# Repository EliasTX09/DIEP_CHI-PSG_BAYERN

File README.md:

# ⛳ Golf Battle 3D – Arcade-Multiplayer-Minigolf für Android (Godot 4)

Echtes 3D-Arcade-Minigolf: 15 Bahnen in 4 Welten, eingebettet in Täler mit Bergen, Klippen, Wäldern und Schluchten,
riskante Abkürzungen, Loopings, Kanonen, Teleporter, Hämmer, Bäche, Lava und Wasser,
bis zu 6 Spieler gleichzeitig, Bots für den Offline-Modus, Schlägertasche mit Upgrades, Truhen, Ligen
und ein täglicher „Golden Shot“. **Alles** – Bahnen, Modelle, Effekte, Shader und Sounds – wird per Code erzeugt.
Es gibt keine `.glb`-, `.fbx`- oder `.wav`-Dateien im Projekt.

> Engine: **Godot 4.5** (GDScript, Mobile-Renderer, Jolt Physics) · Backend: **Supabase** (optional) ·
> Build: **GitHub Actions** → `GolfBattle3D.apk`
> Hochformat (einhändig) · Web-Portal für Accounts in [`webapp/`](webapp) (GitHub Pages)
> Die `index.html` im Repo-Root gehört nicht zum Spiel.

> **Umbau-Stand:** Hochformat-Hauptmenü (Arena-Auswahl mit 3D-Hintergrund, Tab-Leiste Spielen · Tasche · Pass ·
> Freunde · Shop), Hochformat-HUD, kostenloser Battle Pass (28-Tage-Saisons, 30 Stufen), Bahnen in Berg-Tälern
> statt im offenen Wasser, eine riskante Abkürzung pro Bahn, Hindernisse auf der Bahn (Bach, Rough, Baumstämme,
> Felsen) und die neue Ziel-Vorschau (Gummiband + Punkt-Kette) sind fertig.
> Noch offen: Flyover-Vorschau, Trophäen pro Bahn, adaptive Bots, Clans.

---

## Schnellstart in 4 Schritten

### 1. Supabase einrichten (optional – ohne Backend läuft das Spiel offline mit Bots)

1. Auf [supabase.com](https://supabase.com) ein kostenloses Projekt anlegen.
2. **SQL Editor → New query**: den kompletten Inhalt von [`supabase_schema.sql`](supabase_schema.sql) einfügen
   und **Run** drücken. Das Skript ist wiederholbar (zweimal ausführen schadet nicht) und legt an:
   `profiles`, `clubs`, `inventory`, `friends`, `lobbies`, `lobby_invites`, `match_results`, `game_link_codes`
   inklusive Row-Level-Security, dazu den Storage-Bucket **`avatars`** für Profilbilder (öffentlich lesbar, max. 512 KB).
3. **Authentication → Sign In / Providers**:
   - **„Allow anonymous sign-ins“ einschalten** (für den Sofort-Gast-Login per Geräte-ID).
   - **Email** aktiviert lassen (zum Verknüpfen des Gast-Accounts mit E-Mail + Passwort).
     Für schnelle Tests kannst du „Confirm email“ ausschalten.
4. **Authentication → URL Configuration**: als **Site URL** und unter **Redirect URLs** die Adresse deines
   Web-Portals eintragen (z.B. `https://<dein-name>.github.io/<repo>/`), damit Bestätigungs- und
   Passwort-Mails zurück aufs Portal führen.
5. **Project Settings → API**: die **Project URL** und den **anon public**-Key kopieren.
   ⚠️ **Niemals** den `service_role`-Key verwenden – der gehört nie in eine App.

### 2. Zugangsdaten eintragen – eine der beiden Varianten

**Variante A (empfohlen): GitHub Secrets** – dann stehen die Werte nicht im Repository.
GitHub → dein Repo → **Settings → Secrets and variables → Actions → New repository secret**:

| Name | Wert |
|---|---|
| `SUPABASE_URL` | `https://xxxx.supabase.co` |
| `SUPABASE_ANON_KEY` | dein anon public Key |
| `WEB_PORTAL_URL` (optional) | Adresse des Web-Portals; ohne Angabe: `https://<besitzer>.github.io/<repo>/` |

Der Workflow schreibt sie beim Build in `config/backend.cfg`.

**Variante B:** direkt in [`config/backend.cfg`](config/backend.cfg) eintragen:

```ini
[supabase]
url="https://xxxx.supabase.co"
anon_key="eyJhbGciOi..."
```

Solange dort die Platzhalter stehen, startet das Spiel im **Offline-Modus** (Bots, lokaler Speicherstand).

### 3. Auf GitHub pushen

Der Workflow [`.github/workflows/build_android.yml`](.github/workflows/build_android.yml) läuft bei jedem Push auf
`main` (und auf Entwicklungs-Branches `ccr-*`) sowie manuell über **Actions → Build Android APK → Run workflow**.
Er

1. nutzt Godot 4.5.2 mit Export-Templates, Android-SDK und Java 17 (Docker-Image `barichello/godot-ci:4.5.2`),
2. erzeugt einen Debug-Keystore,
3. importiert das Projekt und bricht bei jedem Skriptfehler ab,
4. beweist, dass wirklich **Jolt Physics** rechnet (Physik-Fingerabdruck),
5. führt einen Headless-Smoke-Test aus (Logik, Physik, alle Bahnen, Bots, komplette Partie, Touch-Gesten, Menü),
6. exportiert **`GolfBattle3D.apk`** und lädt sie als **Artifact** hoch,
7. veröffentlicht sie bei Pushes auf `main` zusätzlich als **GitHub Release** (`build-<Nummer>`).

Parallel laufen ein Shader-Check mit Software-Rendering (inkl. Screenshots) und ein Test des SQL-Schemas
gegen eine echte PostgreSQL-Datenbank.

### 4. APK herunterladen und installieren

1. GitHub → **Actions** → letzter grüner Lauf von „Build Android APK“ → unten bei **Artifacts** auf
   **GolfBattle3D-apk** klicken (ZIP entpacken) – oder bei Builds von `main` unter **Releases** die APK laden.
2. APK aufs Handy kopieren (oder direkt am Handy herunterladen) und antippen.
3. Android fragt nach **„Installation aus unbekannten Quellen“** → für den Browser/Dateimanager erlauben.
4. Installieren, starten – fertig. Das Spiel läuft im Hochformat.

Voraussetzungen am Gerät: Android 7+ mit **arm64** (praktisch alle Geräte seit ca. 2017).
Der Mobile-Renderer nutzt Vulkan; auf Geräten ohne Vulkan wechselt Godot automatisch auf OpenGL.

### 5. Web-Portal veröffentlichen (Account, Profilbild, Freunde)

Das Portal liegt in [`webapp/`](webapp) – reines HTML/CSS/JavaScript ohne externe Bibliotheken.

1. GitHub → **Settings → Pages → Source: „GitHub Actions“** (falls auf GitHub Pages dieses Repositorys schon
   eine andere Seite läuft: Achtung, das Portal ersetzt sie – dann lieber ein eigenes Repository dafür nutzen).
2. Die Secrets `SUPABASE_URL` und `SUPABASE_ANON_KEY` setzen (wie oben).
3. **Actions → „Web-Portal veröffentlichen“ → Run workflow** (läuft bewusst nur manuell und vom Standard-Branch).

**So verbindet man das Spiel mit dem Web-Account:**
1. Im Spiel: **Profil → „Account verknüpfen / Registrieren“** öffnet das Portal im Browser.
2. Dort registrieren bzw. einloggen, Profilbild hochladen, Freunde verwalten.
3. **„Spiel-Code erzeugen“** (Passwort bestätigen) → 8-stelliger Code, 10 Minuten und nur einmal gültig.
4. Code im Spiel unter **Profil → Spiel-Code → Einlösen** eingeben. Das Spiel erhält dabei eine **eigene** Anmeldung
   (die Browser-Sitzung wird nie weitergegeben) und speichert sie verschleiert in `user://auth.json`.
5. Hatte das Spiel schon Fortschritt als Gast und der Web-Account ebenfalls, wird der Stand des Accounts geladen
   und der Gast-Stand als Sicherung (`user://save_backup_*.json`) abgelegt – es geht nichts still verloren.
   Ist der Web-Account neu, übernimmt er den Gast-Fortschritt.

Ein Direkt-Sprung vom Browser zurück ins Spiel (Deep-Link) ist **nicht** eingebaut – dafür bräuchte die APK
einen eigenen Android-Build mit Intent-Filter. Der Code wird deshalb abgetippt.

---

## Steuerung

| Geste | Wirkung |
|---|---|
| Am Ball ziehen und loslassen | Schlag: nach hinten ziehen wie ein Gummiband (das Band spannt sich hinter dem Ball zum Finger), loslassen schießt nach vorn. Vorn zeigt eine Punkt-Kette auf dem Boden, wo der Ball aufkommt, abprallt und ausrollt (echte Simulation). Länge der Kette = Guide-Wert des Schlägers, Größe des Landerings = Accuracy |
| Ein Finger irgendwo sonst | Kamera 360° drehen und neigen |
| Zwei Finger | Pinch-Zoom |
| Auge-Button | Vogelperspektive |
| „ROLLEN / CHIP“ | Putt am Boden oder Chip-Schlag in die Luft |
| Spin-Widget | Topspin, Backspin, Seiten-Effet |
| Smiley-Button | Emotes & Quick-Chat („Nice Shot!“, „Oops!“, 🔥, 😂 …) |
| Android-Zurück | schließt Fenster bzw. fragt vor dem Beenden |

## Inhalte

- **Welten & Bahnen (15 + Daily):** Emerald Valley (5), Volcano Canyon (4), Cyber Neon City (3), Pirate Cove / Sky Ruins (3),
  jede Welt mit eigenem Himmel, Licht, Nebel und Shadern (Wasser, Lava, Neon-Hologramm, Holzplanken, Wasserfall …).
- **Landschaft:** Jede Bahn liegt in einem Tal: Randstreifen, Wiesen-Böschungen, Felsterrassen und Klippen,
  Bergrücken mit Schnee, ein Bergkranz im Nebel, Tannen-/Laub-/Palmenwälder bzw. tote Bäume und Hochhäuser (Neon),
  Wasserfall-Kaskade oder Lavastrom, Piratenbucht mit Meer und Schiff. Unter Sprüngen und Stücken ohne Bande klafft
  eine Schlucht. Wer das Gelände neben der Bahn berührt, ist **aus** (+1 Strafschlag).
- **Abkürzungen:** Auf jeder Bahn außer der geraden Einsteiger-Bahn e1 (und dem Golden Shot) gibt es eine Öffnung in
  der Bande: ein schmaler Steg ohne Banden führt über eine Schlucht durch ein Felsentor zu einem Sprungpad, das den
  Ball mit Schwung aufs Grün (bzw. ein späteres Fairway-Stück) schießt. Vom Steg gerollt = Schlucht = Aus, zu
  langsam = der Ball bleibt auf dem Steg; wer seitlich versetzt oder mit falschem Tempo aufs Pad kommt, landet versetzt.
- **Hindernisse:** Bäche quer über die Bahn mit schmalem Holzsteg, tiefes Rough am Rand, Baumstämme und Felsbrocken,
  Lianen-Bögen, Sandbunker.
- **Bahn-Baukasten:** Rampen, Steilkurven, Spiralen, Loopings, Brücken, Lücken, Boost-Pads, Windzonen, Teleporter,
  Kanonen, Laser-Tore, Sandbunker, Windmühlen, Pendel-Hämmer, Schiebeblöcke, fahrende Plattformen.
- **Multiplayer:** Gast-Login per Geräte-ID, Verknüpfen mit E-Mail/Passwort, Spielername, Avatar-Farbe und -Rahmen,
  bis zu 6 Spieler gleichzeitig (alle schlagen parallel), Live-Rangliste, Emotes, Freunde (Suche per Name oder
  Freundes-Code, Anfragen, Online-Status), private Lobby mit 4-stelligem Raum-Code oder Einladung, Welt und 3/5/9 Runden.
- **Progression:** 16 Schläger (4 Kategorien × 4 Seltenheiten, Werte Power/Accuracy/Spin/Guide, Upgrades mit Coins + Karten),
  6 Bälle mit kleinen Boni, 6 Trails, 5 Loch-Explosionen mit Screen-Shake und Bass, 4 Truhen-Slots mit Timern
  (oder sofort per Gems), Trophäen, 5 Ligen und Trophäen-Pfad.
- **Extras:** Style-Punkte („Air Time!“, „Bank Shot!“, „Close Call!“, Hole-in-One) mit Bonus-Coins,
  Golden Shot (ein Schlag pro Tag, Belohnung nach Abstand zur Fahne), Replay des besten Schlags in Zeitlupe.
- **Sound:** prozeduraler Synthesizer (`AudioStreamGenerator`) – Abschlag je nach Kraft, Abpraller auf Holz/Stein/Metall,
  Wind bei hohen Sprüngen, Wasser-/Lava-Platscher, Loch-Sound + Fanfare, UI-Klicks, Truhen-Jingle.

## Projektstruktur

```
project.godot                     Godot 4.5, Mobile-Renderer, Jolt Physics, Hochformat (720 x 1280), MSAA, Schatten
export_presets.cfg                Android-Export (arm64, INTERNET, ACCESS_NETWORK_STATE, VIBRATE)
supabase_schema.sql               Tabellen, RLS-Policies, Trigger, Spiel-Code-Funktionen, Storage-Bucket "avatars"
config/backend.cfg                Supabase-URL + anon-Key + Web-Portal-Adresse (Platzhalter = Offline-Modus)
.github/workflows/build_android.yml   Tests + APK + Schema-Test + Portal-Browsertest
.github/workflows/pages.yml           Web-Portal auf GitHub Pages veröffentlichen (manuell)
webapp/                           Web-Portal: index.html, app.js, style.css, config.js
scenes/                           MainMenuView.tscn, Game.tscn, GameHUD.tscn
shaders/                          17 eigene Shader (Gelände, Gras/Grün, Sand, Wasser, Lava, Himmel, Neon, Portal, Ball-Skins …)
scripts/autoload/                 GameManager (Speicherstand, Wirtschaft, Truhen, Ligen),
                                  AuthManager (Login, Session, Web-Code), ProfileManager (Profilbild),
                                  NetworkManager (Profil-Sync, Freunde, Lobbys, Realtime), SoundManager (Synthesizer)
scripts/data/Catalog.gd           Alle Spieldaten (Schläger, Bälle, Truhen, Ligen, Welten)
scripts/gameplay/                 Ball3D, CameraRig3D, CourseBuilder3D (inkl. Abkürzungs-Planung), TrackKit, Terrain3D (Gelände),
                                  WorldTheme (Landschaft, Licht), Gadgets, Obstacles, ShotSim (Vorhersage), BotBrain (KI),
                                  Match3D (Spielablauf)
scripts/fx/                       Materialien, Partikel, Flora (Bäume, Felsen), Ball-Skins, Explosionen, Schlägermodelle, Emoji-Icons
scripts/ui/                       MainMenu (MainMenuView), MenuPages, Preview3D, GameHUD, UIKit, UIIcon, UIAvatar
tests/                            Smoke-Test, Schein-Supabase-Server, Screenshot-Runner, Physik-Fingerabdruck,
                                  SQL-Tests, web/portal_test.js (Browser-Test)
docs/ARCHITECTURE.md              Architektur und Schnittstellen
```

## Ehrlicher Status

| Bereich | Stand |
|---|---|
| Import, alle Skripte und Shader kompilieren | in CI geprüft |
| Jolt Physics aktiv | in CI per Physik-Fingerabdruck nachgewiesen |
| Ball-Physik vs. Vorhersage, Out-of-Bounds, Einlochen auf allen Bahnen | in CI geprüft (Smoke-Test) |
| Bots spielen alle 15 Bahnen | in CI geprüft |
| Komplette Partie mit Bots inkl. Belohnungen, Golden Shot, Touch-Gesten | in CI geprüft |
| Hochformat-Menü, alle Seiten, Battle Pass | in CI geprüft (Aufbau, Kernaktionen, Layout: alles im Bild, keine Überlappung, Mindestbreite ≤ 720 px); Freunde/Lobby im Online-Zustand mit Testdaten gegen den Schein-Server |
| Battle-Pass-Stand im Cloud-Spielstand | gegen den Schein-Server geprüft; Saisons richten sich nach der Geräte-Uhr |
| Darstellung aller Welten, HUD und Menü | per Software-Rendering in CI gerendert (720×1280 und 720×1600) und angesehen |
| SQL-Schema + RLS-Regeln | in CI gegen PostgreSQL 16 getestet |
| Login-Ablauf im Spiel (Gast, Web-Code, Profil-Abgleich, Profilbild) | in CI gegen einen **lokalen Schein-Server** getestet – prüft das Spiel, nicht den echten Supabase-Server |
| Spiel-Codes, Profilbild-Pfade, Storage-Regeln | in CI gegen PostgreSQL 16 getestet (Supabase-Storage nachgebildet) |
| Web-Portal (Registrieren, Profilbild, Freunde, Spiel-Code, XSS-Schutz, Handy-Breite) | in CI im Browser (Chromium) gegen simulierte Supabase-Antworten getestet |
| Supabase-Login, Freunde, Lobbys, Realtime, Portal gegen ein **echtes** Supabase-Projekt | **nicht getestet** |
| Hochformat-HUD | in CI geprüft (Layout oben/unten, Daumenzone) |
| Gelände-Tal | in CI geprüft: liegt auf allen 16 Bahnen überall unter dem Belag, Schluchten unter allen Sprüngen/Flügen, Aus-Grenze greift neben der Bahn; Bau ~40 ms pro Bahn |
| Abkürzungen | in CI geprüft auf allen 14 Bahnen: Vorhersage landet auf dem Grün, seitlich vom Steg = Aus, zu langsam = bleibt auf dem Steg; echter Ball auf e2, v3, n3, p1 landet wie vorhergesagt (≤ 0,1 m Abweichung). Die Ersparnis wird gemessen (11–101 m Weg), nicht pauschal „2 Schläge“ |
| Hindernisse (Bach, Rough, Stamm, Fels) | in CI geprüft (Wirkung + Bots locht weiter auf allen 15 Bahnen ein) |
| Spiel auf einem echten Android-Gerät | **nicht getestet** (Performance, Touch-Gefühl, Safe-Areas bitte selbst prüfen) |
| APK-Export + Artifact `GolfBattle3D-apk` | in CI gebaut (Entwicklungs-Branch) |
| GitHub-Release-Schritt | läuft nur auf `main` – **erst nach dem Merge geprüft** |

Bekannte Warnung: Jolt meldet in der CI gelegentlich „job system exceeded the maximum number of jobs“ (Godot-interne Meldung, bisher ohne erkennbare Auswirkung auf die Tests).

Bekannte Grenzen: Online-Matches sind „Client-autoritativ“ (jeder meldet seine eigenen Schläge) – für ein Spiel unter
Freunden okay, gegen Cheater nicht abgesichert. Es gibt keine Echtgeld-Käufe; Gems verdient man im Spiel.

## Hinweise

- **Name:** „Golf Battle“ ist der Name eines existierenden kommerziellen Spiels. Für eine Veröffentlichung im
  Play Store solltest du einen eigenen Namen wählen (`config/name` in `project.godot`, Paketname in `export_presets.cfg`).
- **Release-Build:** Die CI baut eine Debug-APK mit Debug-Keystore. Für den Play Store brauchst du einen eigenen
  Release-Keystore (als GitHub Secret) und ein AAB.
- **Lokal entwickeln:** Ordner in Godot 4.5 öffnen, `res://scenes/MainMenuView.tscn` ist die Startszene.
  Tests: `godot --headless --fixed-fps 60 res://tests/Smoke.tscn`.

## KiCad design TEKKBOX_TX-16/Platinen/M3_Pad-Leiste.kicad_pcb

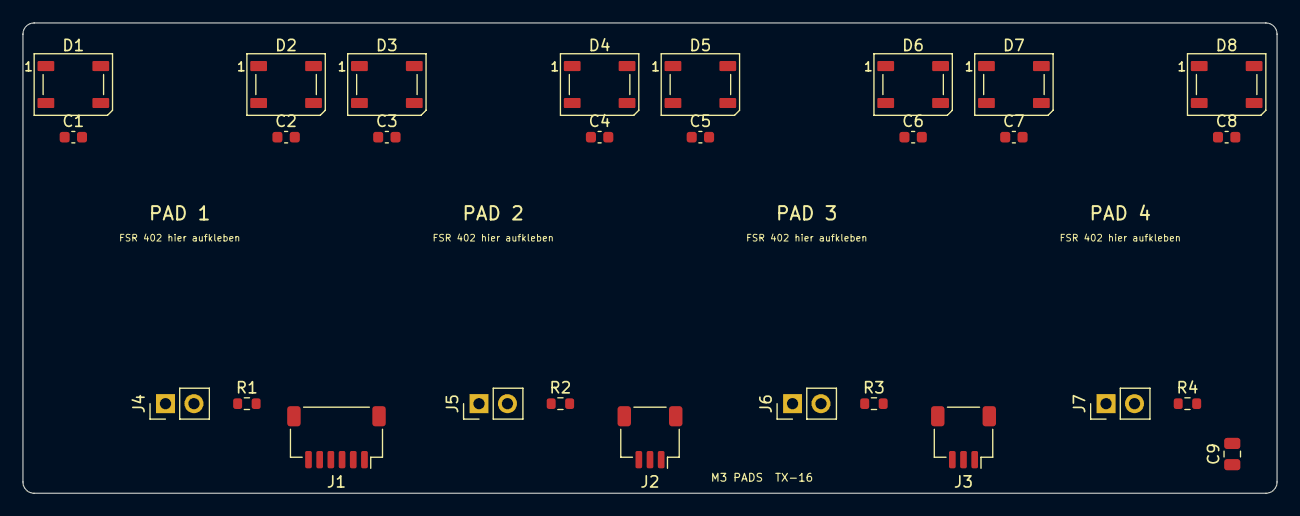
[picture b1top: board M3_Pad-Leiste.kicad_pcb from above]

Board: 2 copper layers, 112.0 x 42.0 mm, 28 parts (0 on the bottom side), 16 nets, no tracks yet.

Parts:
C1, C2, C3, C4, C5, C6, C7, C8: 100nF; C_0603_1608Metric
C9: 10uF; C_0805_2012Metric
D1, D2, D3, D4, D5, D6, D7, D8: WS2812B; LED_WS2812B_PLCC4_5.0x5.0mm_P3.2mm
J1: Pads analog; JST_SH_SM06B-SRSS-TB_1x06-1MP_P1.00mm_Horizontal
J2: LED IN; JST_SH_SM03B-SRSS-TB_1x03-1MP_P1.00mm_Horizontal
J3: LED OUT; JST_SH_SM03B-SRSS-TB_1x03-1MP_P1.00mm_Horizontal
J4: FSR1; PinHeader_1x02_P2.54mm_Vertical
J5: FSR2; PinHeader_1x02_P2.54mm_Vertical
J6: FSR3; PinHeader_1x02_P2.54mm_Vertical
J7: FSR4; PinHeader_1x02_P2.54mm_Vertical
R1, R2, R3, R4: 10k; R_0603_1608Metric

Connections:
+3V3: J1.1, J4.1, J5.1, J6.1, J7.1
+5V: C1.1, C2.1, C3.1, C4.1, C5.1, C6.1, C7.1, C8.1, C9.1, D1.4, D2.4, D3.4, D4.4, D5.4, D6.4, D7.4, D8.4, J2.1, J3.1
FSR1: J1.3, J4.2, R1.1
FSR2: J1.4, J5.2, R2.1
FSR3: J1.5, J6.2, R3.1
FSR4: J1.6, J7.2, R4.1
GND: C1.2, C2.2, C3.2, C4.2, C5.2, C6.2, C7.2, C8.2, C9.2, D1.2, D2.2, D3.2, D4.2, D5.2, D6.2, D7.2, D8.2, J1.2, J1.MP, J2.2, J2.MP, J3.2, J3.MP, R1.2, R2.2, R3.2, R4.2
L1: D1.1, D2.3
L2: D2.1, D3.3
L3: D3.1, D4.3
L4: D4.1, D5.3
L5: D5.1, D6.3
L6: D6.1, D7.3
L7: D7.1, D8.3
LED_IN: D1.3, J2.3
LED_OUT: D8.1, J3.3

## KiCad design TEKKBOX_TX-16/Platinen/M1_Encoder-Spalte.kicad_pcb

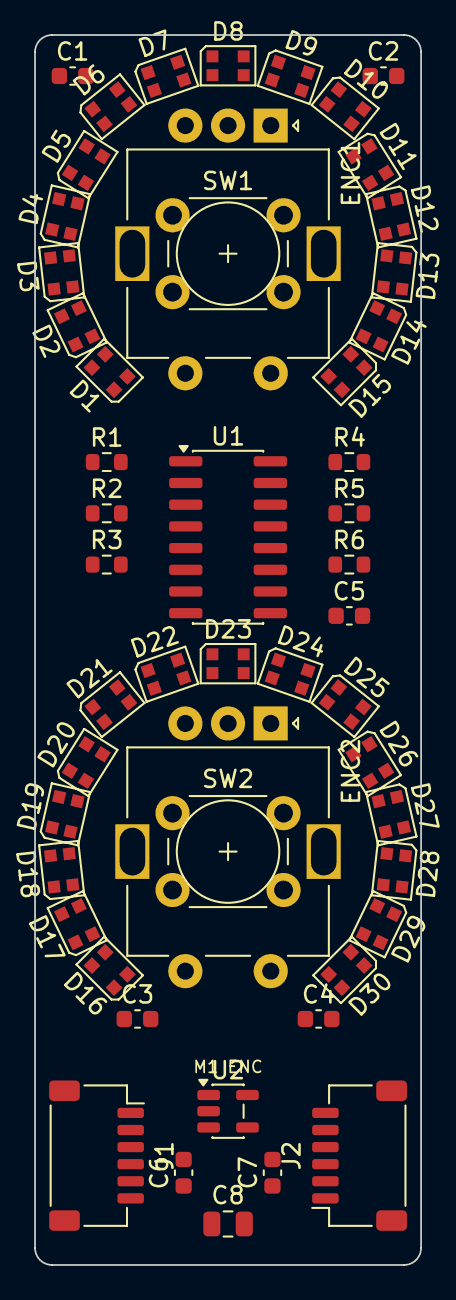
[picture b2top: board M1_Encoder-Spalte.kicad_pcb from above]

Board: 2 copper layers, 22.6 x 72.0 mm, 52 parts (0 on the bottom side), 44 nets, no tracks yet.

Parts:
C1, C2, C3, C4, C5: 100nF; C_0603_1608Metric
C6, C7: 1uF; C_0603_1608Metric
C8: 10uF; C_0805_2012Metric
D1, D2, D3, D4, D5, D6, D7, D8, D9, D10, D11, D12, D13, D14, D15, D16, D17, D18, D19, D20, D21, D22, D23, D24, D25, D26, D27, D28, D29, D30: WS2812B-2020; LED_WS2812B-2020_PLCC4_2.0x2.0mm
ENC1, ENC2: EC11 20mm; RotaryEncoder_Alps_EC11E-Switch_Vertical_H20mm
J1: Kette IN; JST_SH_SM06B-SRSS-TB_1x06-1MP_P1.00mm_Horizontal
J2: Kette OUT; JST_SH_SM06B-SRSS-TB_1x06-1MP_P1.00mm_Horizontal
R1, R2, R3, R4, R5, R6: 10k; R_0603_1608Metric
SW1, SW2: Taster 6x6 (statt Encoder); SW_PUSH_6mm_H7.3mm
U1: 74HC165; SOIC-16_3.9x9.9mm_P1.27mm
U2: AP2112K-3.3; SOT-23-5

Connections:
+3V3: C5.1, C7.1, R1.1, R2.1, R3.1, R4.1, R5.1, R6.1, U1.5, U1.6, U1.16, U2.5
+5V: C1.1, C2.1, C3.1, C4.1, C6.1, C8.1, D1.4, D2.4, D3.4, D4.4, D5.4, D6.4, D7.4, D8.4, D9.4, D10.4, D11.4, D12.4, D13.4, D14.4, D15.4, D16.4, D17.4, D18.4, D19.4, D20.4, D21.4, D22.4, D23.4, D24.4, D25.4, D26.4, D27.4, D28.4, D29.4, D30.4, J1.1, J2.1, U2.1, U2.3
CLK: J1.4, J2.4, U1.2
ENC1_A: ENC1.A, R1.2, U1.11
ENC1_B: ENC1.B, R2.2, U1.12
ENC1_SW: ENC1.S1, R3.2, SW1.1, U1.13
ENC2_A: ENC2.A, R4.2, U1.14
ENC2_B: ENC2.B, R5.2, U1.3
ENC2_SW: ENC2.S1, R6.2, SW2.1, U1.4
GND: C1.2, C2.2, C3.2, C4.2, C5.2, C6.2, C7.2, C8.2, D1.2, D2.2, D3.2, D4.2, D5.2, D6.2, D7.2, D8.2, D9.2, D10.2, D11.2, D12.2, D13.2, D14.2, D15.2, D16.2, D17.2, D18.2, D19.2, D20.2, D21.2, D22.2, D23.2, D24.2, D25.2, D26.2, D27.2, D28.2, D29.2, D30.2, ENC1.C, ENC1.MP, ENC1.S2, ENC2.C, ENC2.MP, ENC2.S2, J1.2, J1.MP, J2.2, J2.MP, SW1.2, SW2.2, U1.8, U1.15, U2.2
L1: D1.1, D2.3
L2: D2.1, D3.3
L3: D3.1, D4.3
L4: D4.1, D5.3
L5: D5.1, D6.3
L6: D6.1, D7.3
L7: D7.1, D8.3
L8: D8.1, D9.3
L9: D9.1, D10.3
L10: D10.1, D11.3
L11: D11.1, D12.3
L12: D12.1, D13.3
L13: D13.1, D14.3
L14: D14.1, D15.3
L15: D15.1, D16.3
L16: D16.1, D17.3
L17: D17.1, D18.3
L18: D18.1, D19.3
L19: D19.1, D20.3
L20: D20.1, D21.3
L21: D21.1, D22.3
L22: D22.1, D23.3
L23: D23.1, D24.3
L24: D24.1, D25.3
L25: D25.1, D26.3
L26: D26.1, D27.3
L27: D27.1, D28.3
L28: D28.1, D29.3
L29: D29.1, D30.3
LED_IN: D1.3, J1.6
LED_OUT: D30.1, J2.6
QH_OUT: J1.5, U1.9
SER_IN: J2.5, U1.10
SH_LD: J1.3, J2.3, U1.1

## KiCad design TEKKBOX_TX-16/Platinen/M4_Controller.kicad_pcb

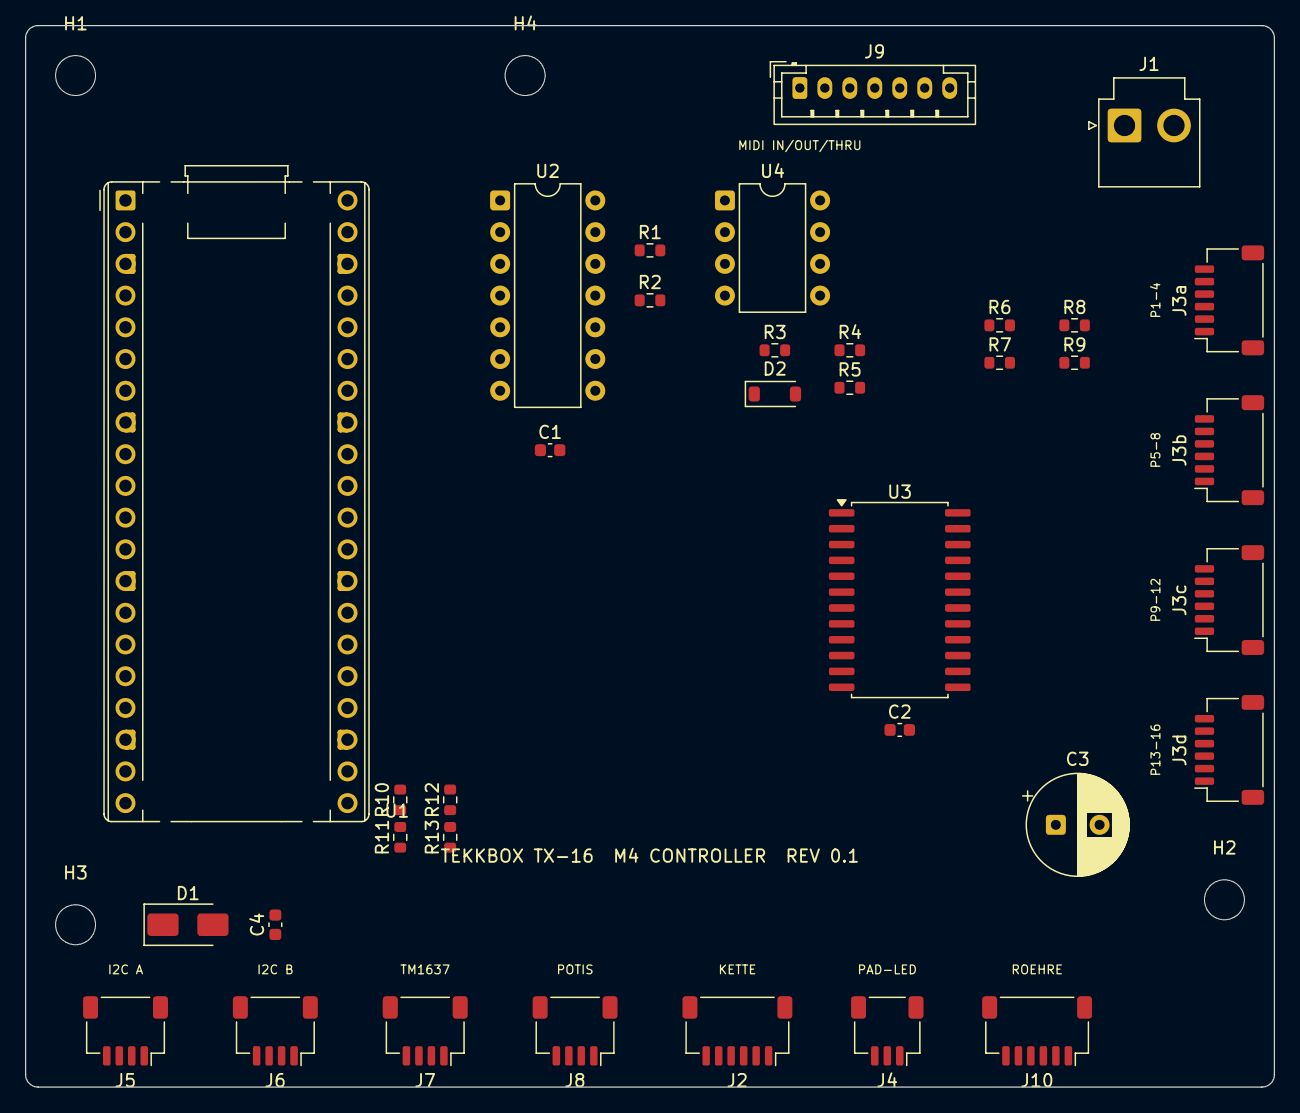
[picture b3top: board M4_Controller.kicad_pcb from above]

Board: 2 copper layers, 100.0 x 85.0 mm, 40 parts (0 on the bottom side), 57 nets, no tracks yet.

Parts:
C1, C2, C4: 100nF; C_0603_1608Metric
C3: 470uF; CP_Radial_D8.0mm_P3.50mm
D1: SS14; D_SMA
D2: 1N4148W; D_SOD-123
H1, H2, H3, H4: M3; MountingHole_3.2mm_M3
J1: 5V IN; JST_VH_B2P-VH_1x02_P3.96mm_Vertical
J2: KETTE; JST_SH_SM06B-SRSS-TB_1x06-1MP_P1.00mm_Horizontal
J3a: PADS 1-4; JST_SH_SM06B-SRSS-TB_1x06-1MP_P1.00mm_Horizontal
J3b: PADS 5-8; JST_SH_SM06B-SRSS-TB_1x06-1MP_P1.00mm_Horizontal
J3c: PADS 9-12; JST_SH_SM06B-SRSS-TB_1x06-1MP_P1.00mm_Horizontal
J3d: PADS 13-16; JST_SH_SM06B-SRSS-TB_1x06-1MP_P1.00mm_Horizontal
J4: PAD-LED; JST_SH_SM03B-SRSS-TB_1x03-1MP_P1.00mm_Horizontal
J5: I2C A; JST_SH_SM04B-SRSS-TB_1x04-1MP_P1.00mm_Horizontal
J6: I2C B; JST_SH_SM04B-SRSS-TB_1x04-1MP_P1.00mm_Horizontal
J7: TM1637; JST_SH_SM04B-SRSS-TB_1x04-1MP_P1.00mm_Horizontal
J8: POTIS; JST_SH_SM04B-SRSS-TB_1x04-1MP_P1.00mm_Horizontal
J9: MIDI DIN; JST_PH_B7B-PH-K_1x07_P2.00mm_Vertical
J10: ROEHRE; JST_SH_SM06B-SRSS-TB_1x06-1MP_P1.00mm_Horizontal
R1, R2, R6, R8: 33R; R_0603_1608Metric
R3: 220R; R_0603_1608Metric
R4: 470R; R_0603_1608Metric
R5: 10k; R_0603_1608Metric
R7, R9: 10R; R_0603_1608Metric
R10, R11, R12, R13: 4k7; R_0603_1608Metric
U1: Raspberry Pi Pico 2; RaspberryPi_Pico_Common_THT
U2: 74AHCT125; DIP-14_W7.62mm
U3: CD74HC4067; SOIC-24W_7.5x15.4mm_P1.27mm
U4: 6N138; DIP-8_W7.62mm

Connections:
+3V3: C2.1, C4.1, J3a.1, J3b.1, J3c.1, J3d.1, J5.2, J6.2, J7.2, J8.2, R4.1, R6.1, R8.1, R10.1, R11.1, R12.1, R13.1, U1.36, U3.24, U4.8
+5V: C1.1, C3.1, D1.2, J1.1, J2.1, J4.1, J10.1, U2.14
CLK: J2.4, U1.24
GND: C1.2, C2.2, C3.2, C4.2, J1.2, J2.2, J2.MP, J3a.2, J3a.MP, J3b.2, J3b.MP, J3c.2, J3c.MP, J3d.2, J3d.MP, J4.2, J4.MP, J5.1, J5.MP, J6.1, J6.MP, J7.1, J7.MP, J8.1, J8.MP, J9.7, J10.2, J10.MP, R5.2, U1.3, U1.8, U1.13, U1.18, U1.23, U1.28, U1.33, U1.38, U2.1, U2.4, U2.7, U2.9, U2.10, U2.12, U2.13, U3.12, U3.15, U4.5
LED_MAIN: J2.6, R1.2
LED_MAIN_3V: U1.9, U2.2
LED_MAIN_5V: R1.1, U2.3
LED_PADS: J4.3, R2.2
LED_PADS_3V: U1.10, U2.5
LED_PADS_5V: R2.1, U2.6
MIDI_IN4: J9.1, R3.1
MIDI_IN5: D2.2, J9.2, U4.3
MIDI_IN_A: D2.1, R3.2, U4.2
MIDI_OUT4: J9.3, R6.2
MIDI_OUT5: J9.4, R7.2
MIDI_OUT_TX: R7.1, U1.1
MIDI_RX: R4.2, U1.2, U4.6
MIDI_THRU4: J9.5, R8.2
MIDI_THRU5: J9.6, R9.2
MIDI_THRU_TX: R9.1, U1.6
MUX_S0: U1.11, U3.10
MUX_S1: U1.12, U3.11
MUX_S2: U1.26, U3.14
MUX_S3: U1.27, U3.13
MUX_SIG: U1.31, U3.1
OPTO_VB: R5.1, U4.7
PAD1: J3a.3, U3.9
PAD2: J3a.4, U3.8
PAD3: J3a.5, U3.7
PAD4: J3a.6, U3.6
PAD5: J3b.3, U3.5
PAD6: J3b.4, U3.4
PAD7: J3b.5, U3.3
PAD8: J3b.6, U3.2
PAD9: J3c.3, U3.23
PAD10: J3c.4, U3.22
PAD11: J3c.5, U3.21
PAD12: J3c.6, U3.20
PAD13: J3d.3, U3.19
PAD14: J3d.4, U3.18
PAD15: J3d.5, U3.17
PAD16: J3d.6, U3.16
POT_MASTER: J8.3, U1.32
POT_PHONES: J8.4, U1.34
QH: J2.5, U1.21
RELAY: J10.6, U1.7
SCL_A: J5.4, R11.2, U1.17
SCL_B: J6.4, R13.2, U1.20
SDA_A: J5.3, R10.2, U1.16
SDA_B: J6.3, R12.2, U1.19
SH_LD: J2.3, U1.22
TM_CLK: J7.3, U1.4
TM_DIO: J7.4, U1.5
TUBE_CS: J10.5, U1.29
TUBE_MOSI: J10.4, U1.15
TUBE_SCK: J10.3, U1.14
VSYS: D1.1, U1.39

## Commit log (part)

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2026-05-06 Add initial HTML structure for live stream page
